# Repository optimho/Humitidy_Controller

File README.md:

# Humitidy_Controller

This a 2 speed fan controller with a humidity sensor.
The setpoint will be controllable via bluetooth. 
The firmware is not complete to do this as yet.

The files include eagle cad schematics and a zipped fabrication ready gerber files.

#TODO#
1) write firmware to read the humitity
2) Figure out a way of setting the humidity setpoint via bluetooth on a smart phone 
3) Figure out a way to read the humidity and temperature via bluetooth onto a smart phone
4) Write interface software for a smart phone so that the control and readout look nice.
5) Include the ability for the device to measure humidity and temperature from a remote low energy bluetooth device.
6) device has the ability to log temperature and humidity. 
7)

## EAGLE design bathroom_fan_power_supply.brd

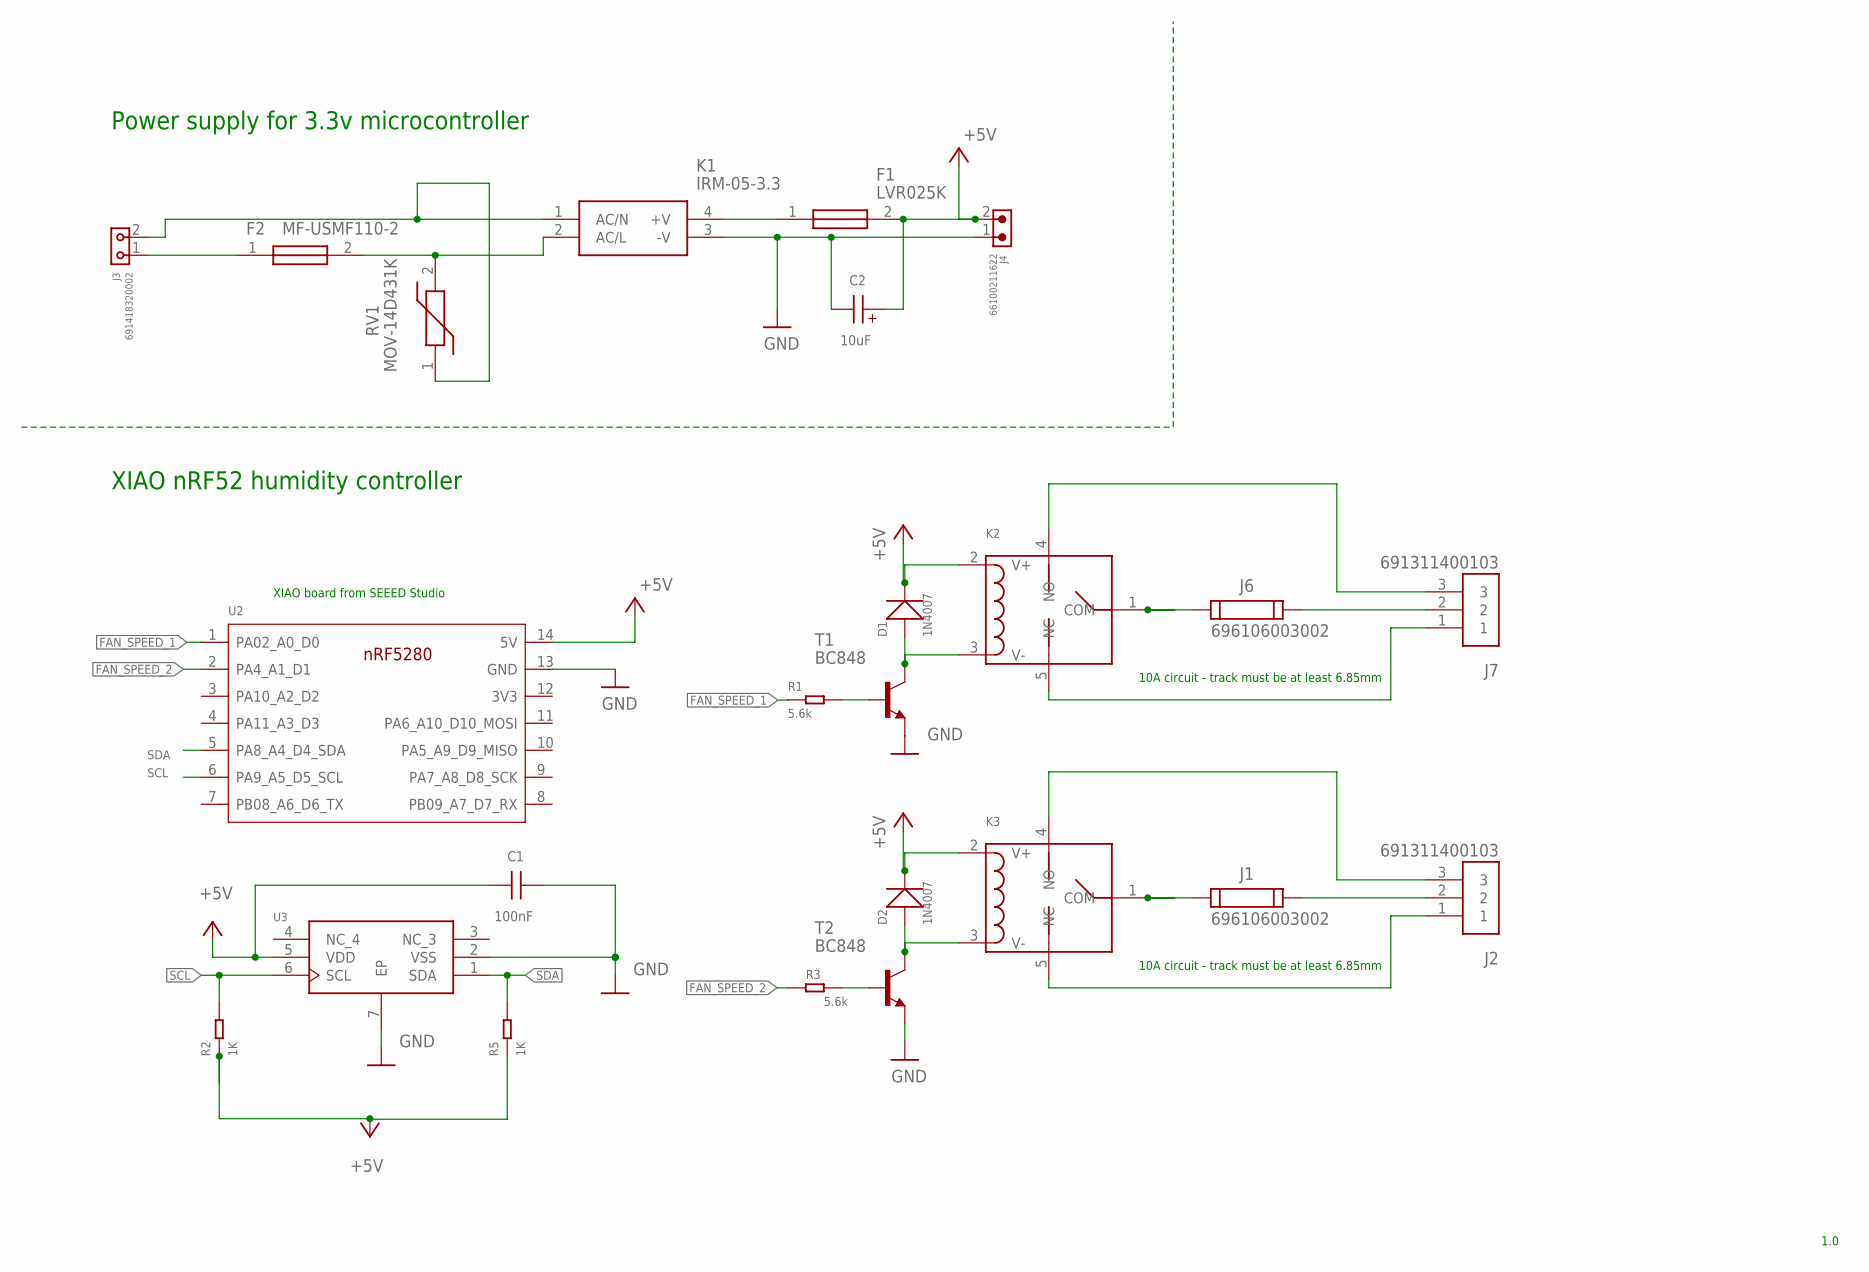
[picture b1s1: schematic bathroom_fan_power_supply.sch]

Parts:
C1: 100nF; WCAP-CSGP_0805_H0.8_R
C2: 10uF; WCAP-AS5H_4X5.5(DXL)
D1, D2: 1N4007; DO-214AC
F1: LVR025K
F2: MF-USMF110-2; FUSC3226X85N
J1, J6: 696106003002
J2, J7: 691311400103; TERMINALBLOCK_PLUGGABLE-3-7.62MM
J3: 691418320002
J4: 66100211622
K1: IRM-05-3.3; IRM-05-3.3_1
K2, K3: HLS8L-DC3V-S-C; REY5-19.0X15.0X15.0MM
R1, R3: 5.6k; R0805
R2, R5: 1K; R0805
RV1: MOV-14D431K; MOV-14D(5.2MM-T)
T1, T2: BC848; SOT23
U2: MOUDLE14P-2.54-21X17.8MM
U3: SHT21; 6-TDFN

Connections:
+5V: C1.1, C2.1 (+), D1.2 (-), D2.2 (-), F1.2, J4.2, K2.2 (V+), K3.2 (V+), R2.1, R5.1, U2.14 (5V), U3.5 (VDD)
FAN_SPEED_1: R1.1, U2.1 (PA02_A0_D0)
FAN_SPEED_2: R3.1, U2.2 (PA4_A1_D1)
GND: C1.2, C2.2 (-), J4.1, K1.3 (-V), T1.2 (E), T2.2 (E), U2.13 (GND), U3.2 (VSS), U3.7 (EP)
HIGHCURRENT1: J1.1, K3.1 (COM)
unnamed: F2.2, K1.2 (AC/L), RV1.2
unnamed: F2.1, J3.1
unnamed: F1.1, K1.4 (+V)
unnamed: J6.1, K2.1 (COM)
unnamed: J3.2, K1.1 (AC/N), RV1.1
unnamed: J6.2, J7.2
unnamed: R1.2, T1.1 (B)
unnamed: J7.1, K2.5 (NC)
unnamed: J7.3, K2.4 (NO)
unnamed: D2.1 (+), K3.3 (V-), T2.3 (C)
unnamed: R3.2, T2.1 (B)
unnamed: J2.1, K3.5 (NC)
unnamed: J2.3, K3.4 (NO)
unnamed: J1.2, J2.2
unnamed: D1.1 (+), K2.3 (V-), T1.3 (C)
SCL: R2.2, U2.6 (PA9_A5_D5_SCL), U3.6 (SCL)
SDA: R5.2, U2.5 (PA8_A4_D4_SDA), U3.1 (SDA)

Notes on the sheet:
1.0
Power supply for 3.3v microcontroller
10A circuit - track must be at least 6.85mm
XIAO nRF52 humidity controller
XIAO board from SEEED Studio

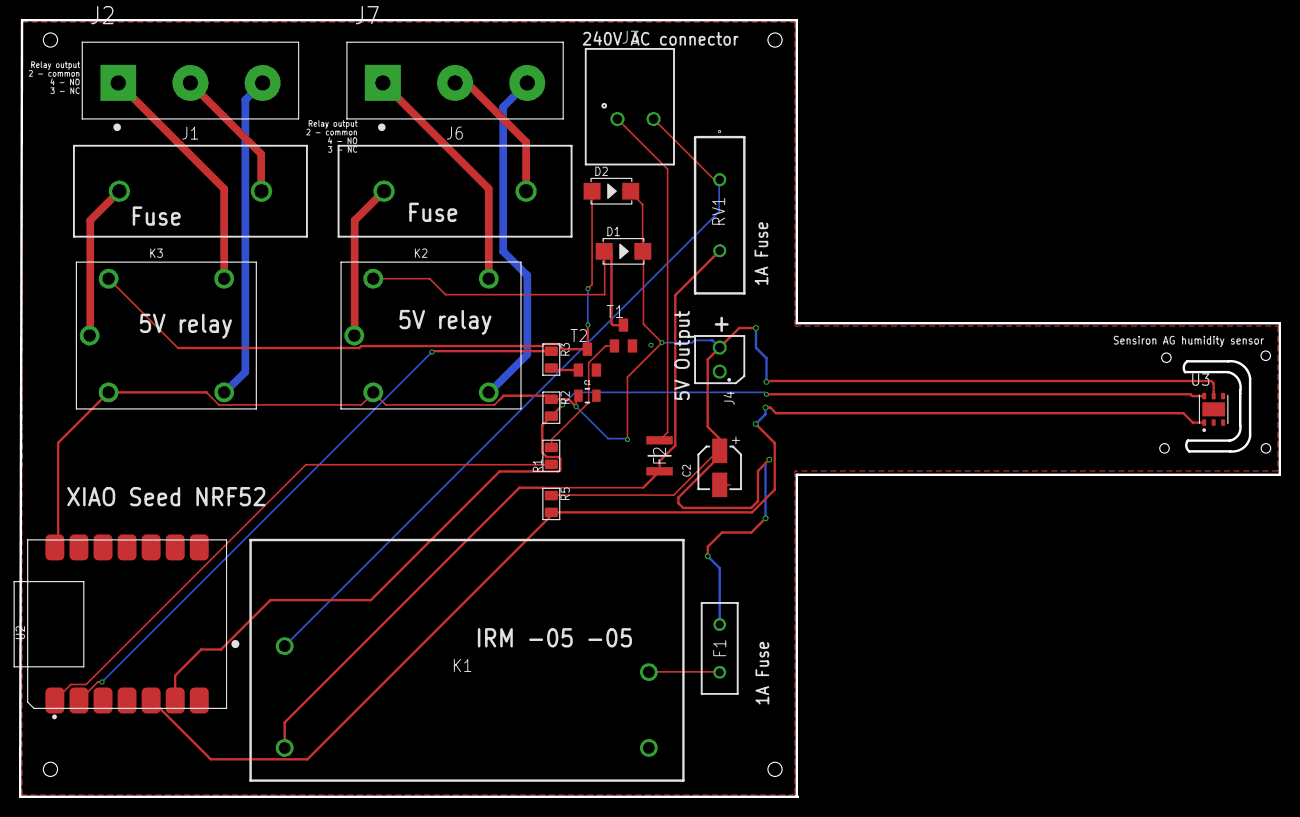
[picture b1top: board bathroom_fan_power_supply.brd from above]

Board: 2 copper layers, 133.0 x 82.0 mm, 24 parts (0 on the bottom side), 22 nets.

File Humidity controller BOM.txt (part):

Partlist exported from /home/michael/EAGLE/projects/barthroom automatic fan/bathroom_fan_power_supply.sch at 11/09/22 2:58 PM

Part Value          Device                                     Package                          Description                                                                                   ARROW_PART_NUMBER ARROW_PRICE-STOCK                                                             CERAMIC-TYPE CONTACT-RESISTANCE CREATED_BY    DATASHEET-URL                                                DESCRIPTION                                                                          DF          DIAMETER DIGIKEY_PART_NO DIGIKEY_PART_NUMBER                                           ENDURANCE GENDER HEIGHT I-LEAK I-RIPPLE IR IR-UL IR-VDE L      MANUFACTURER     MANUFACTURER_NAME MANUFACTURER_PART_NUMBER MATES         MOUNT MOUSER_PART_NUMBER MOUSER_PRICE-STOCK                                                                                 MPN            OPERATING-TEMPERATURE PACKAGE         PACKAGING                                                                                     PART-NUMBER    PCB-CABLE-PANEL PINS PITCH  POPULARITY QMIN RISO  SIZE TECHNICAL-REFERENCE     TOL-R TYPE     VALUE          VR      WIRE                                WORKING-VOLTAGE WORKING-VOLTAGE-UL WORKING-VOLTAGE-VDE
C1   100nF          WCAP-CSGP_0805_H0.8_885012207016_10V(DC)_R WCAP-CSGP_0805_H0.8_R            WCAP-CSGP MLCCs 0805                                                                                                                                                                          X7R Class II                                  https://www.we-online.com/redexpert/spec/885012207016?ae                                                                                          5%                                                                                                                  0.8mm                                                                                                                   SMT                                                                                                                                        -55 up to +125 °C                                                                                                                    885012207016                                         -    5GOhm 0805 X7R0805104K010DFCT10000                100nF          10V(DC)                                                                                           
C2   10uF           WCAP-AS5H_4X5.5_865230340001               WCAP-AS5H_4X5.5(DXL)             WCAP-AS5H Aluminium Electrolytic Capacitors                                                                                                                                                                                                 https://www.we-online.com/redexpert/spec/865230340001?ae                                                                                          22%         4mm                                                                                    5000h            5.5mm  3uA    17mA                                                                                                                                                                                                                                                 -40 °C up to +105 °C                                                                                                                 865230340001                                                         ASDB055100M016DVCTAE000                10uF           16V(DC)                                                                                           
D1   1N4007         DIODE-GEN-PURPOSE-1KV-1A(DO-214AC)         DO-214AC                         304010013                                                                                                                                                                                                                                                                                                                                                                                                                                                                                                                                                                                                                                                                                                                                                             1N4007                                                                                                                                                                                                                                                          1N4007                                                                                                           
D2   1N4007         DIODE-GEN-PURPOSE-1KV-1A(DO-214AC)         DO-214AC                         304010013                                                                                                                                                                                                                                                                                                                                                                                                                                                                                                                                                                                                                                                                                                                                                             1N4007                                                                                                                                                                                                                                                          1N4007                                                                                                           
F1   LVR025K        LVR025K                                    LVR025K                          Fuse,resettable,PolySwitch,thermal and overcurrent protection,PCB mount,240Vac,250mA          LVR025K           https://www.arrow.com/en/products/lvr025k/littelfuse?region=europe                                                                                                                       Fuse,resettable,PolySwitch,thermal and overcurrent protection,PCB mount,240Vac,250mA                                                                                                                     18.8mm                                                         LITTELFUSE        LVR025K                                      650-LVR025K        https://www.mouser.co.uk/ProductDetail/Littelfuse/LVR025K?qs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
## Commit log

2022-09-11 initial commit of humidity controller
2022-09-11 Added a Bill of materials
2022-09-11 Update README.md
    Added todos to the readme

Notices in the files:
parts and their libraries:
Wurth_Capacitors_WCAP-CSGP: Copyright: Würth Elektronik
